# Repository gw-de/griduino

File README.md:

# griduino
Power grid quality measurement with Arduino (student project @ Siemens Technik Akademie Berlin)

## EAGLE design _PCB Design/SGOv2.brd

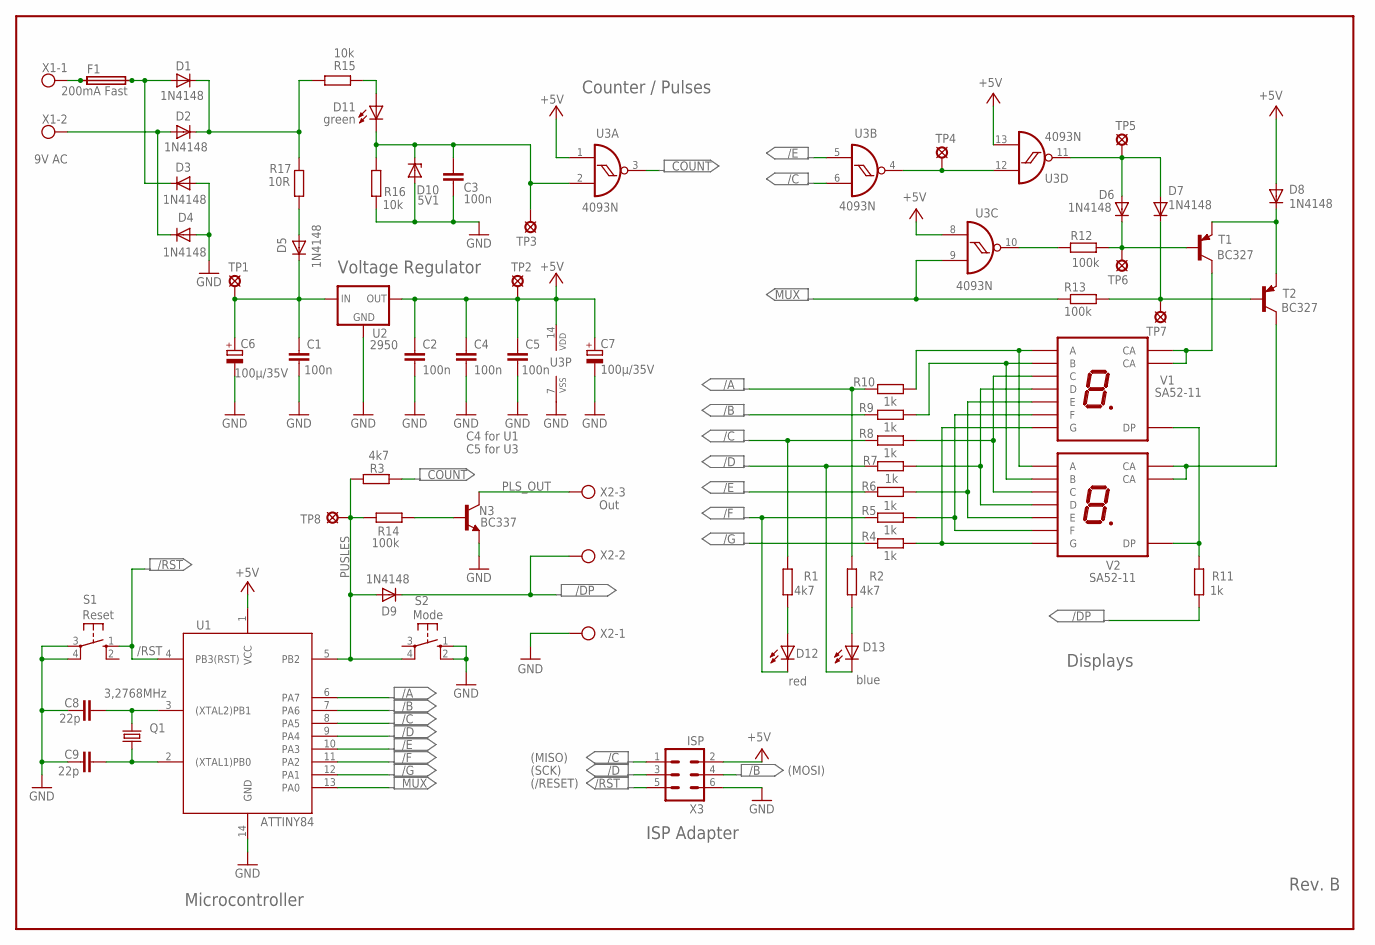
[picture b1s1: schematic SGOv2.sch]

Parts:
C1, C2, C3, C4, C5: 100n; C025-024X044
C6, C7: 100µ/35V; E2,5-7
C8, C9: 22p; C025-024X044
D1, D2, D3, D4, D5, D6, D7, D8, D9: 1N4148; DO35-10
D10: 5V1; DO35Z10
D11: green; LED3MM
D12: red; LED3MM
D13: blue; LED3MM
F1: 200mA Fast; SHK20Q
F2: FUSESH22,5; SH22,5
N3: BC337; TO92
Q1: 3,2768MHz; HC49/S
R1, R2, R3: 4k7; 0207/10
R4, R5, R6, R7, R8, R9, R10, R11: 1k; 0207/10
R12, R13, R14: 100k; 0207/10
R15, R16: 10k; 0207/10
R17: 10R; 0207/10
S1: Reset; B3F-10XX
S2: Mode; B3F-10XX
T1, T2: BC327; TO92
TP1: V+; LSP10
TP2: +5V; LSP10
TP3: C-V5; LSP10
TP4: /EC; LSP10
TP5: EC; LSP10
TP6: B-N1; LSP10
TP7: B-N2; LSP10
TP8: PLS; LSP10
U1: ATTINY84; DIL14
U2: 2950; TO92
U3: 4093N; DIL14
V1, V2: SA52-11; KB-SX52-11
X1: 9V AC; W237-102
X2: Out; W237-103
X3: ISP; ML6

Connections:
+5V: C2.1, C4.1, C5.1, C7.+, D8.A, TP2.MP, U1.1 (VCC), U2.1 (OUT), U3.1 (I0), U3.8 (I0), U3.13 (I1), U3.14 (VDD), X3.2
/A: R2.2, R10.2, U1.6 (PA7)
/B: R9.2, U1.7 (PA6), X3.4
/C: R1.2, R8.2, U1.8 (PA5), U3.6 (I1), X3.1
/D: D13.K (C), R7.2, U1.9 (PA4), X3.3
/DP: D9.C, R11.1, X2.2
/E: R6.2, U1.10 (PA3), U3.5 (I0)
/F: D12.K (C), R5.2, U1.11 (PA2)
/G: R4.2, U1.12 (PA1)
/RST: S1.1 (S), U1.4 (PB3(RST)), X3.5
COUNT: R3.1, U3.3 (O)
GND: C1.2, C2.2, C3.2, C4.2, C5.2, C6.-, C7.-, C8.1, C9.1, D3.A, D4.A, D10.A, N3.3 (E), R16.1, S1.3, S1.4 (P1), S2.1 (S), S2.2 (S1), U1.14 (GND), U2.2 (GND), U3.7 (VSS), X2.1, X3.6
MUX: R13.1, U1.13 (PA0), U3.9 (I1)
unnamed: R10.1, V1.P$7 (A), V2.P$7 (A)
unnamed: R9.1, V1.P$6 (B), V2.P$6 (B)
unnamed: R8.1, V1.P$4 (C), V2.P$4 (C)
unnamed: R7.1, V1.P$2 (D), V2.P$2 (D)
unnamed: R6.1, V1.P$1 (E), V2.P$1 (E)
unnamed: R5.1, V1.P$9 (F), V2.P$9 (F)
unnamed: R4.1, V1.P$10 (G), V2.P$10 (G)
unnamed: T2.1 (C), V2.P$3 (CA), V2.P$8 (CA)
unnamed: T1.1 (C), V1.P$3 (CA), V1.P$8 (CA)
unnamed: D1.A, D3.C, F1.2A, F2.2
unnamed: D2.A, D4.C, X1.2
unnamed: D1.C, D2.C, R15.1, R17.2
unnamed: C1.1, C6.+, D5.C, TP1.MP, U2.3 (IN)
unnamed: D8.C, T1.3 (E), T2.3 (E)
unnamed: D7.C, R13.2, T2.2 (B), TP7.MP
unnamed: D6.C, R12.2, T1.2 (B), TP6.MP
unnamed: R12.1, U3.10 (O)
unnamed: D6.A, D7.A, TP5.MP, U3.11 (O)
unnamed: TP4.MP, U3.4 (O), U3.12 (I0)
unnamed: D12.A, R1.1
unnamed: C8.2, Q1.2, U1.3 ((XTAL2)PB1)
unnamed: D5.A, R17.1
unnamed: C9.2, Q1.1, U1.2 ((XTAL1)PB0)
unnamed: C3.1, D10.C, D11.K (C), R16.2, TP3.MP, U3.2 (I1)
unnamed: D11.A, R15.2
unnamed: R11.2, V1.P$5 (DP), V2.P$5 (DP)
unnamed: F1.1A, F2.1, X1.1
unnamed: D13.A, R2.1
unnamed: N3.2 (B), R14.2
PLS_OUT: N3.1 (C), X2.3
PUSLES: D9.A, R3.2, R14.1, S2.4 (P1), TP8.MP, U1.5 (PB2)

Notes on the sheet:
C4 for U1
C5 for U3
(MOSI)
(MISO)
(SCK)
(/RESET)
ISP Adapter
Microcontroller
Displays
Voltage Regulator
Counter / Pulses
Rev. B

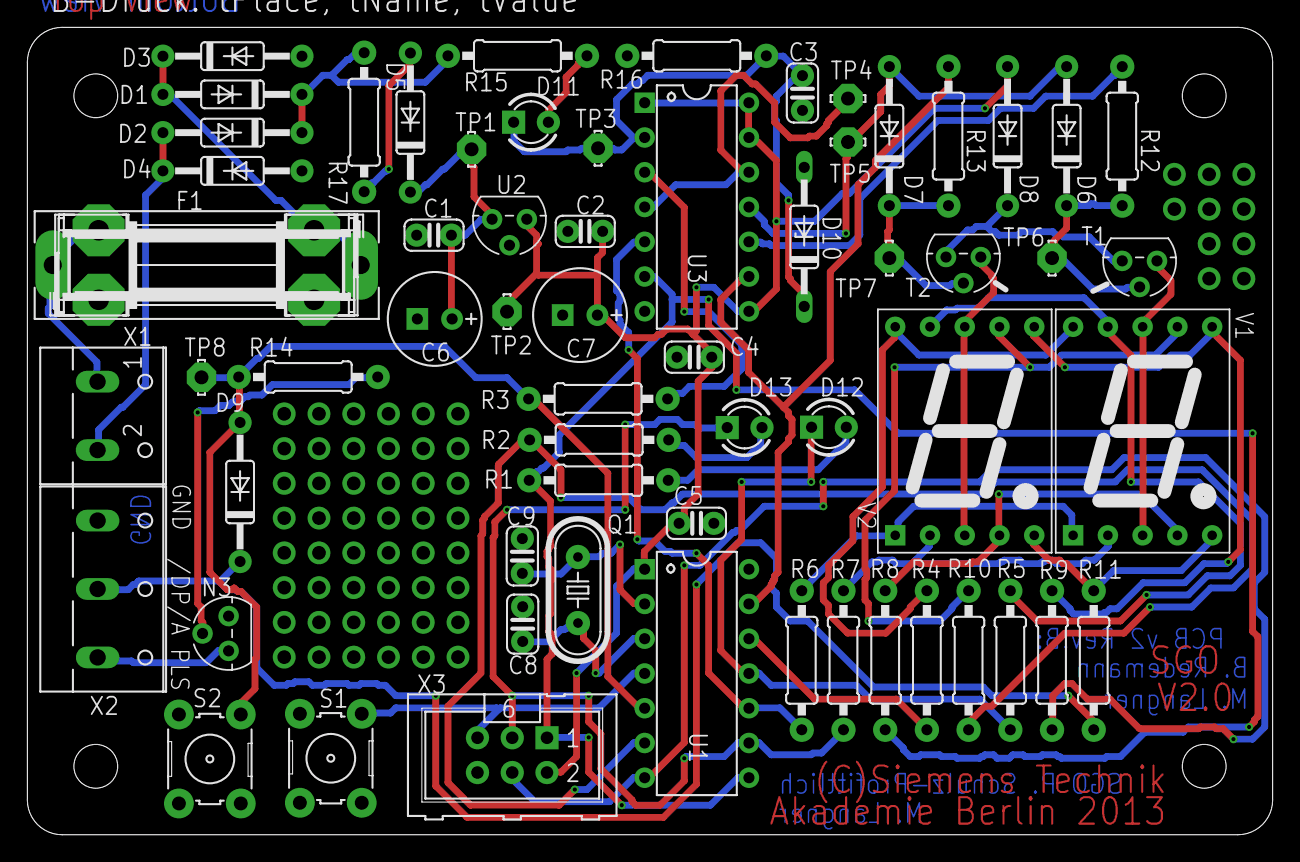
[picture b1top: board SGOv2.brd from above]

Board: 2 copper layers, 91.0 x 59.0 mm, 63 parts (0 on the bottom side), 44 nets.
